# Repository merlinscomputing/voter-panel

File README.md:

# voter-panel
Voter display panel
Test Readme Changes
JJH-2052

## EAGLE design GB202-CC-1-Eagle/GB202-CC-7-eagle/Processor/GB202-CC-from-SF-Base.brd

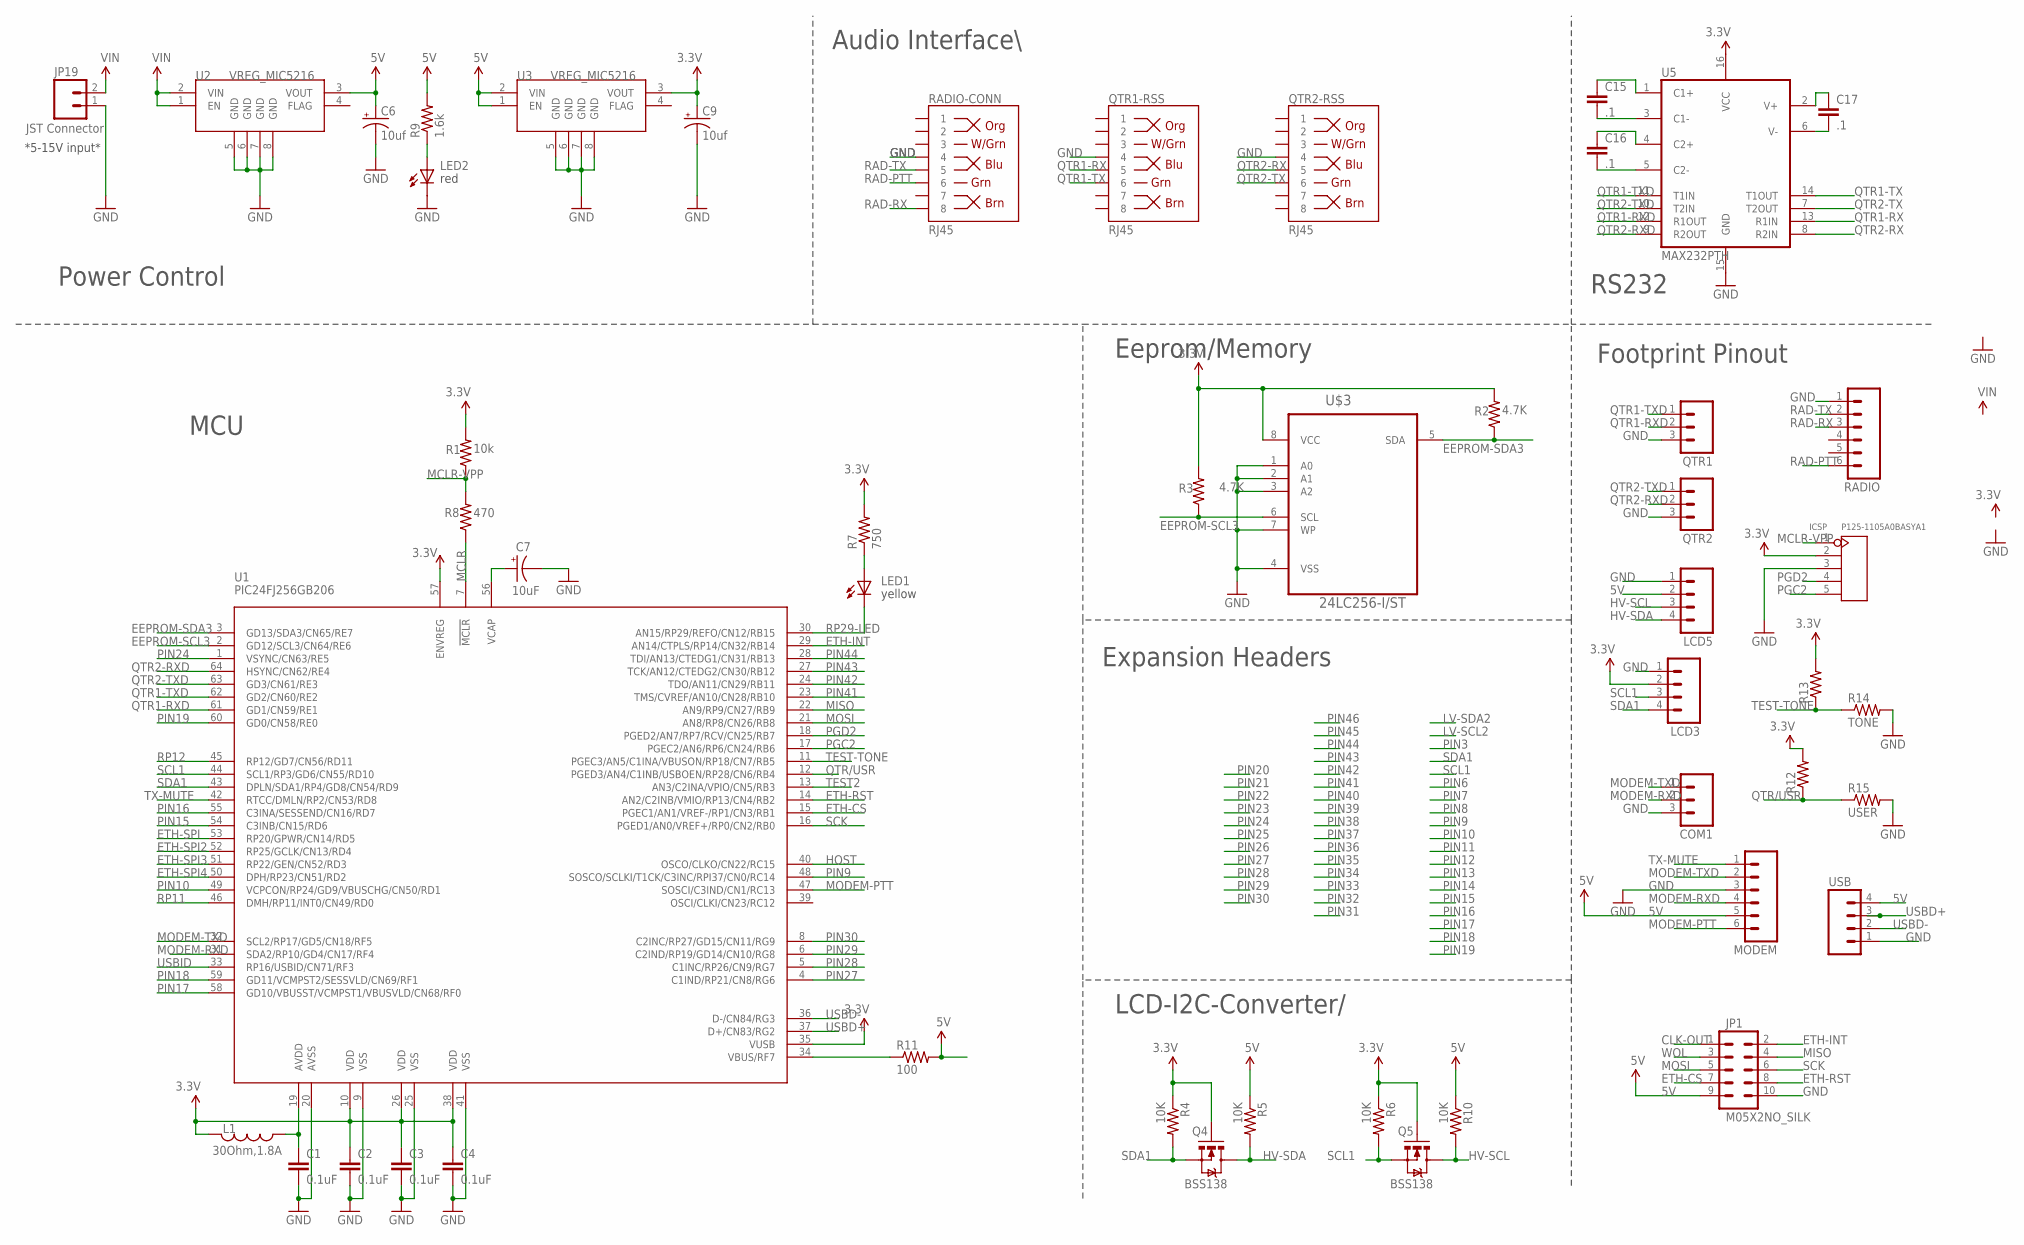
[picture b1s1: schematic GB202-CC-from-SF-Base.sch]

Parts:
C1, C2, C3, C4: 0.1uF; 0402-CAP
C6, C9: 10uf; EIA3216
C7: 10uF; EIA3216
C15, C16, C17: .1; CAP-PTH-SMALL
COM1: M031X03_NO_SILK; 1X03_NO_SILK
ICSP: P125-1105A0BASYA1; H5-2.54
JP1: M05X2NO_SILK; 2X5_NOSILK
JP19: JST Connector; JST-2-SMD
L1: 30Ohm,1.8A; 0603
LCD3, LCD5: M04LONGPADS; 1X04_LONGPADS
LED1: LY L29K-J1K2-26-Z; LED-0603
LED2: LS L29K-G1J2-1-Z; LED-0603
MODEM: M06LONGPADS; 1X06_LONGPADS
Q4, Q5: BSS138; SOT23-3
QTR1, QTR2: M031X03_NO_SILK; 1X03_NO_SILK
QTR1-RSS, QTR2-RSS: RJ45; RJ45-8
R1: 10k; R0402
R2, R3: 4.7K; R0402
R4, R6: 10K; 0402-RES
R5, R10: 10K; 0603-RES
R7: 750; 0603-RES
R8: 470; R0402
R9: 1.6k; 0603-RES
R11: 100; 0402-RES
R12, R13: R-US_R0402; R0402
R14: TONE; R1206
R15: USER; R1206
RADIO: M06LONGPADS; 1X06_LONGPADS
RADIO-CONN: RJ45; RJ45-8
U1: PIC24FJ256GB206; PIC24FXXX_TQFP64
U2, U3: VREG_MIC5216; MSOP8
U5: MAX232PTH; DIL16
U$3: 24LC256-I/ST; SOP65P638X110-8N
USB: M04PTH; 1X04

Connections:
3.3V: C2.1, C3.1, C4.1, C9.A (+), ICSP.2, L1.2, LCD3.2, Q4.1 (G), Q5.1 (G), R1.2, R2.2, R3.2, R4.1, R6.1, R7.2, R12.2, R13.2, U1.10 (VDD), U1.26 (VDD), U1.35 (VUSB), U1.38 (VDD), U1.57 (ENVREG), U3.3 (VOUT), U5.16 (VCC), U$3.8 (VCC)
5V: C6.A (+), JP1.9, LCD5.2, MODEM.5, R5.1, R9.2, R10.1, R11.2, U2.3 (VOUT), U3.1 (EN), U3.2 (VIN), USB.4
CLK-OUT: JP1.1
EEPROM-SCL3: R3.1, U1.2 (GD12/SCL3/CN64/RE6), U$3.6 (SCL)
EEPROM-SDA3: R2.1, U1.3 (GD13/SDA3/CN65/RE7), U$3.5 (SDA)
ETH-CS: JP1.7, U1.15 (PGEC1/AN1/VREF-/RP1/CN3/RB1)
ETH-INT: JP1.2, U1.29 (AN14/CTPLS/RP14/CN32/RB14)
ETH-RST: JP1.8, U1.14 (AN2/C2INB/VMIO/RP13/CN4/RB2)
ETH-SPI: U1.53 (RP20/GPWR/CN14/RD5)
ETH-SPI2: U1.52 (RP25/GCLK/CN13/RD4)
ETH-SPI3: U1.51 (RP22/GEN/CN52/RD3)
ETH-SPI4: U1.50 (DPH/RP23/CN51/RD2)
GND: C1.2, C2.2, C3.2, C4.2, C6.C (-), C7.C (-), C9.C (-), COM1.3, ICSP.3, JP1.10, JP19.1, LCD3.1, LCD5.1, LED2.C, MODEM.3, QTR1.3, QTR1-RSS.4, QTR2.3, QTR2-RSS.4, R14.2, R15.2, RADIO.1, RADIO-CONN.4, U1.9 (VSS), U1.20 (AVSS), U1.25 (VSS), U1.41 (VSS), U2.5 (GND), U2.6 (GND), U2.7 (GND), U2.8 (GND), U3.5 (GND), U3.6 (GND), U3.7 (GND), U3.8 (GND), U5.15 (GND), U$3.1 (A0), U$3.2 (A1), U$3.3 (A2), U$3.4 (VSS), U$3.7 (WP), USB.1
HOST: U1.40 (OSCO/CLKO/CN22/RC15)
HV-SCL: LCD5.3, Q5.3 (D), R10.2
HV-SDA: LCD5.4, Q4.3 (D), R5.2
MCLR: R8.1, U1.7 (!MCLR)
MCLR-VPP: ICSP.1, R1.1, R8.2
MISO: JP1.4, U1.22 (AN9/RP9/CN27/RB9)
MODEM-PTT: MODEM.6, U1.47 (SOSCI/C3IND/CN1/RC13)
MODEM-RXD: COM1.2, MODEM.4, U1.31 (SDA2/RP10/GD4/CN17/RF4)
MODEM-TXD: COM1.1, MODEM.2, U1.32 (SCL2/RP17/GD5/CN18/RF5)
MOSI: JP1.5, U1.21 (AN8/RP8/CN26/RB8)
unnamed: LED1.A, R7.1
unnamed: LED2.A, R9.1
unnamed: C7.A (+), U1.56 (VCAP)
unnamed: C1.1, L1.1, U1.19 (AVDD)
unnamed: R11.1, U1.34 (VBUS/RF7)
unnamed: C15.1, U5.1 (C1+)
unnamed: C15.2, U5.3 (C1-)
unnamed: C16.1, U5.4 (C2+)
unnamed: C16.2, U5.5 (C2-)
unnamed: C17.2, U5.6 (V-)
unnamed: C17.1, U5.2 (V+)
PGC2: ICSP.5, U1.17 (PGEC2/AN6/RP6/CN24/RB6)
PGD2: ICSP.4, U1.18 (PGED2/AN7/RP7/RCV/CN25/RB7)
PIN9: U1.48 (SOSCO/SCLKI/T1CK/C3INC/RPI37/CN0/RC14)
PIN10: U1.49 (VCPCON/RP24/GD9/VBUSCHG/CN50/RD1)
PIN15: U1.54 (C3INB/CN15/RD6)
PIN16: U1.55 (C3INA/SESSEND/CN16/RD7)
PIN17: U1.58 (GD10/VBUSST/VCMPST1/VBUSVLD/CN68/RF0)
PIN18: U1.59 (GD11/VCMPST2/SESSVLD/CN69/RF1)
PIN19: U1.60 (GD0/CN58/RE0)
PIN24: U1.1 (VSYNC/CN63/RE5)
PIN27: U1.4 (C1IND/RP21/CN8/RG6)
PIN28: U1.5 (C1INC/RP26/CN9/RG7)
PIN29: U1.6 (C2IND/RP19/GD14/CN10/RG8)
PIN30: U1.8 (C2INC/RP27/GD15/CN11/RG9)
PIN41: U1.23 (TMS/CVREF/AN10/CN28/RB10)
PIN42: U1.24 (TDO/AN11/CN29/RB11)
PIN43: U1.27 (TCK/AN12/CTEDG2/CN30/RB12)
PIN44: U1.28 (TDI/AN13/CTEDG1/CN31/RB13)
QTR1-RX: QTR1-RSS.5, U5.13 (R1IN)
QTR1-RXD: QTR1.2, U1.61 (GD1/CN59/RE1), U5.12 (R1OUT)
QTR1-TX: QTR1-RSS.6, U5.14 (T1OUT)
QTR1-TXD: QTR1.1, U1.62 (GD2/CN60/RE2), U5.11 (T1IN)
QTR2-RX: QTR2-RSS.5, U5.8 (R2IN)
QTR2-RXD: QTR2.2, U1.64 (HSYNC/CN62/RE4), U5.9 (R2OUT)
QTR2-TX: QTR2-RSS.6, U5.7 (T2OUT)
QTR2-TXD: QTR2.1, U1.63 (GD3/CN61/RE3), U5.10 (T2IN)
QTR/USR: R12.1, R15.1, U1.12 (PGED3/AN4/C1INB/USBOEN/RP28/CN6/RB4)
RAD-PTT: RADIO.6, RADIO-CONN.6
RAD-RX: RADIO.3, RADIO-CONN.8
RAD-TX: RADIO.2, RADIO-CONN.5
RP11: U1.46 (DMH/RP11/INT0/CN49/RD0)
RP12: U1.45 (RP12/GD7/CN56/RD11)
RP29-LED: LED1.C, U1.30 (AN15/RP29/REFO/CN12/RB15)
SCK: JP1.6, U1.16 (PGED1/AN0/VREF+/RP0/CN2/RB0)
SCL1: LCD3.3, Q5.2 (S), R6.2, U1.44 (SCL1/RP3/GD6/CN55/RD10)
SDA1: LCD3.4, Q4.2 (S), R4.2, U1.43 (DPLN/SDA1/RP4/GD8/CN54/RD9)
TEST2: U1.13 (AN3/C2INA/VPIO/CN5/RB3)
TEST-TONE: R13.1, R14.1, U1.11 (PGEC3/AN5/C1INA/VBUSON/RP18/CN7/RB5)
TX-MUTE: MODEM.1, U1.42 (RTCC/DMLN/RP2/CN53/RD8)
USBD+: U1.37 (D+/CN83/RG2), USB.3
USBD-: U1.36 (D-/CN84/RG3), USB.2
USBID: U1.33 (RP16/USBID/CN71/RF3)
VIN: JP19.2, U2.1 (EN), U2.2 (VIN)
WOL: JP1.3

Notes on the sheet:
*5-15V input*
yellow
red
Footprint Pinout
Power Control
MCU
RS232
Audio Interface\
LCD-I2C-Converter/
Expansion Headers
Eeprom/Memory

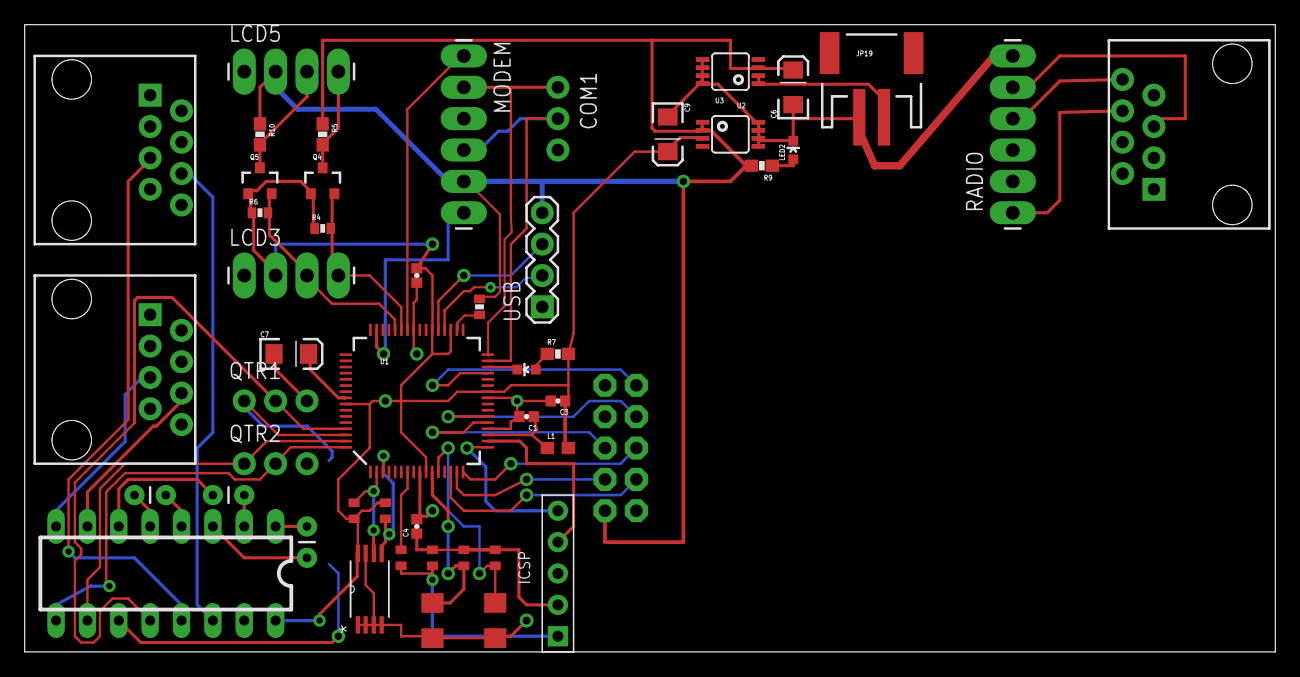
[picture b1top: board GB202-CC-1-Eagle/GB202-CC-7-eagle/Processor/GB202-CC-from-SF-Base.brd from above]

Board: 2 copper layers, 101.3 x 50.8 mm, 49 parts (0 on the bottom side), 51 nets.

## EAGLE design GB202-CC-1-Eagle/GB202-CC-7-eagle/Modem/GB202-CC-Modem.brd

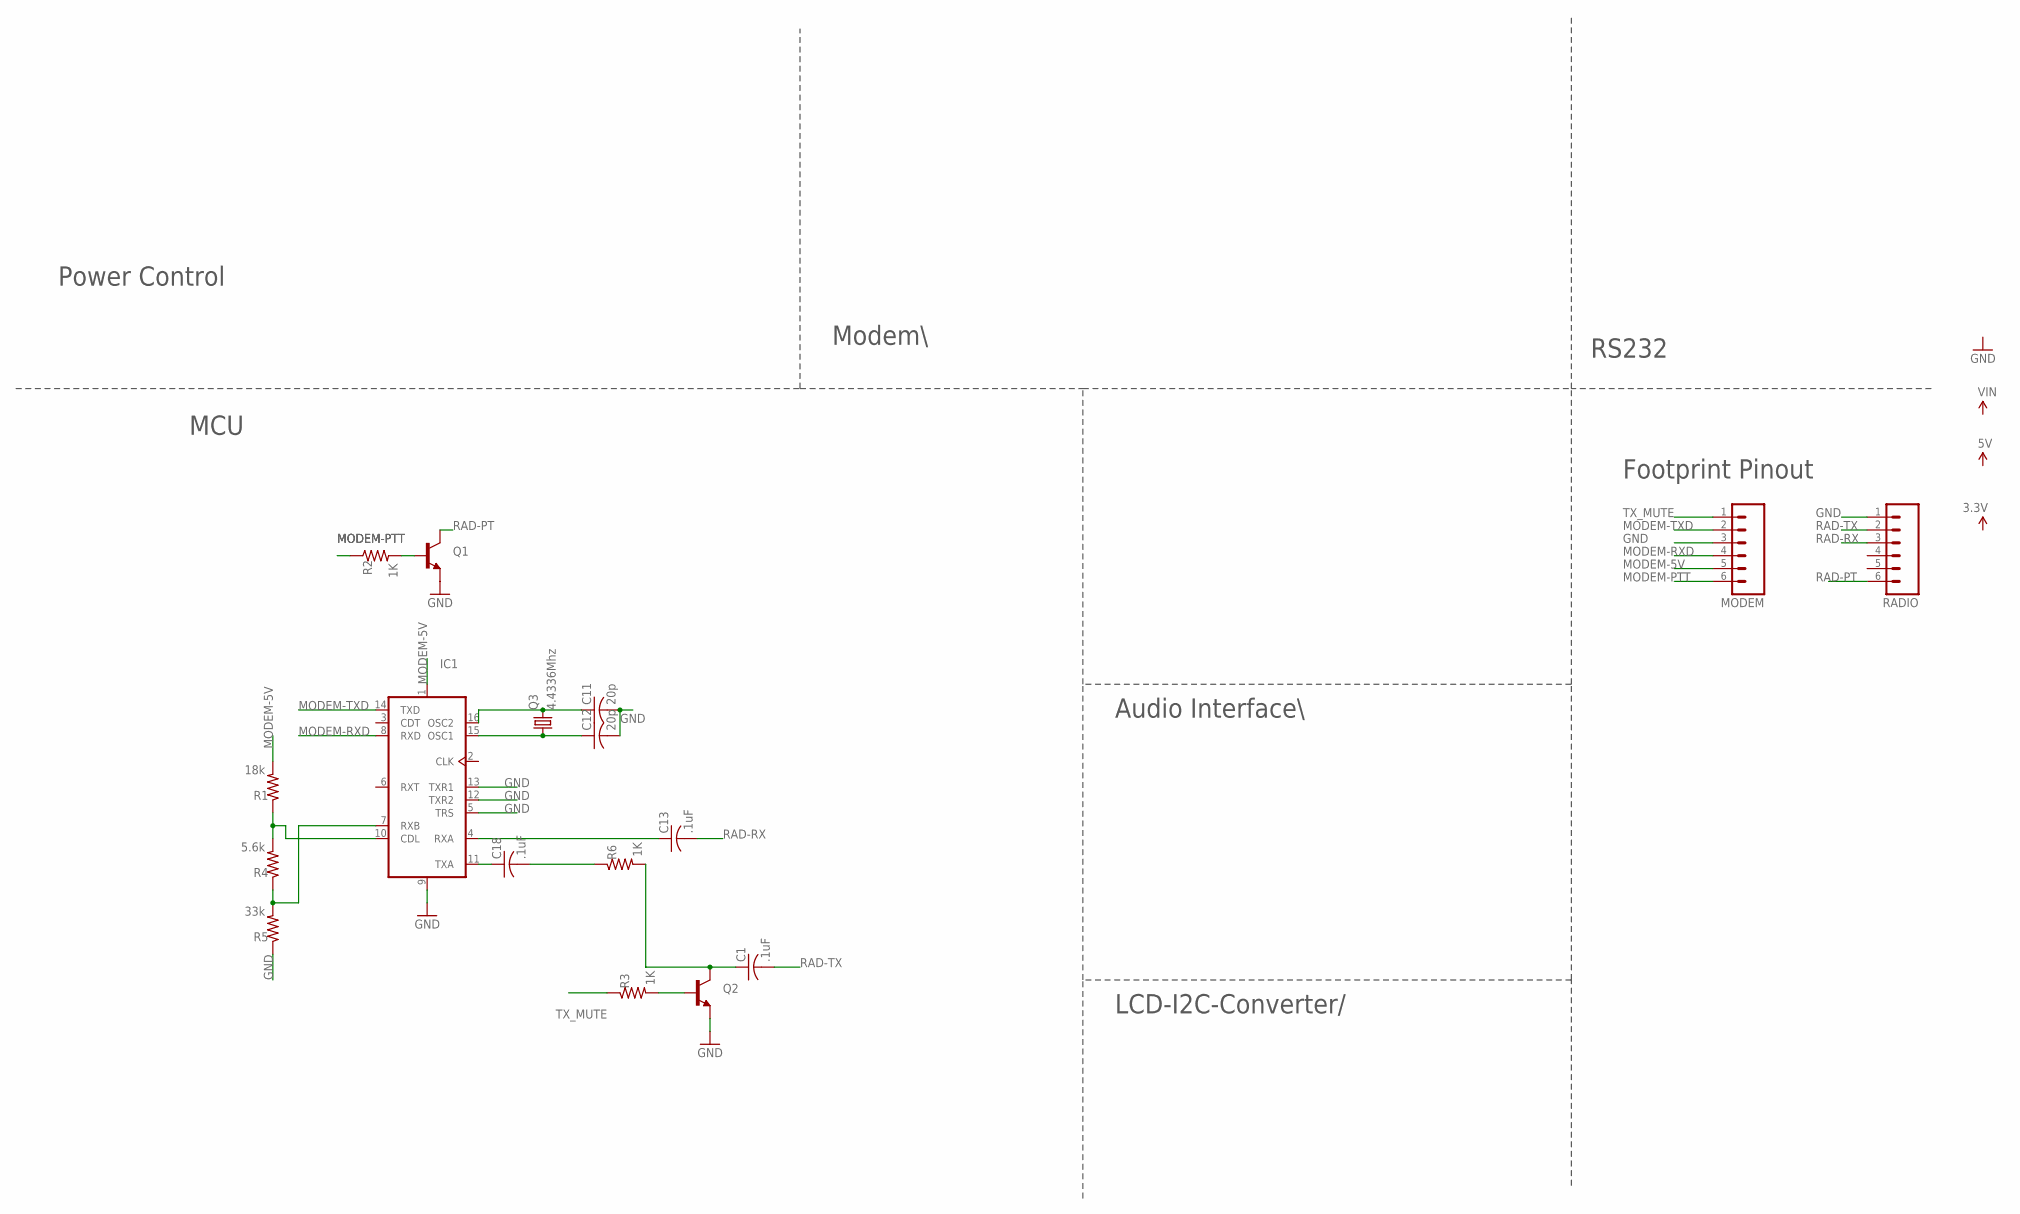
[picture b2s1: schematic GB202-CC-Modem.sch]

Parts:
C1, C13, C18: .1uF; C050-024X044
C11, C12: 20p; C0603
IC1: TCM3105; DIL16
MODEM: M06LONGPADS; 1X06_LONGPADS
Q1: TRANSISTOR_NPNP2N2222A; TO-92
Q2: TRANSISTOR_NPN2N3904; TO-92
Q3: 4.4336Mhz; HC49/S
R1: 18k; AXIAL-0.3
R2, R3, R6: 1K; AXIAL-0.3
R4: 5.6k; AXIAL-0.3
R5: 33k; AXIAL-0.3-KIT
RADIO: M06LONGPADS; 1X06_LONGPADS

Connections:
GND: C11.2, C12.2, IC1.5 (TRS), IC1.9 (VSS), IC1.12 (TXR2), IC1.13 (TXR1), MODEM.3, Q1.3 (E), Q2.1 (E), R5.P$1 (1), RADIO.1
MODEM-5V: IC1.1 (VDD), MODEM.5, R1.P$2 (2)
MODEM-PTT: MODEM.6, R2.P$1 (1)
MODEM-RXD: IC1.8 (RXD), MODEM.4
MODEM-TXD: IC1.14 (TXD), MODEM.2
unnamed: Q1.2 (B), R2.P$2 (2)
unnamed: C1.1, Q2.3 (C), R6.P$2 (2)
unnamed: Q2.2 (B), R3.P$2 (2)
unnamed: C11.1, IC1.16 (OSC2), Q3.2
unnamed: C12.1, IC1.15 (OSC1), Q3.1
unnamed: C13.1, IC1.4 (RXA)
unnamed: IC1.10 (CDL), R1.P$1 (1), R4.P$2 (2)
unnamed: IC1.7 (RXB), R4.P$1 (1), R5.P$2 (2)
unnamed: C18.1, IC1.11 (TXA)
unnamed: C18.2, R6.P$1 (1)
RAD-PT: Q1.1 (C), RADIO.6
RAD-RX: C13.2, RADIO.3
RAD-TX: C1.2, RADIO.2
TX_MUTE: MODEM.1, R3.P$1 (1)

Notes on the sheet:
Footprint Pinout
Power Control
MCU
RS232
Modem\
Audio Interface\
LCD-I2C-Converter/

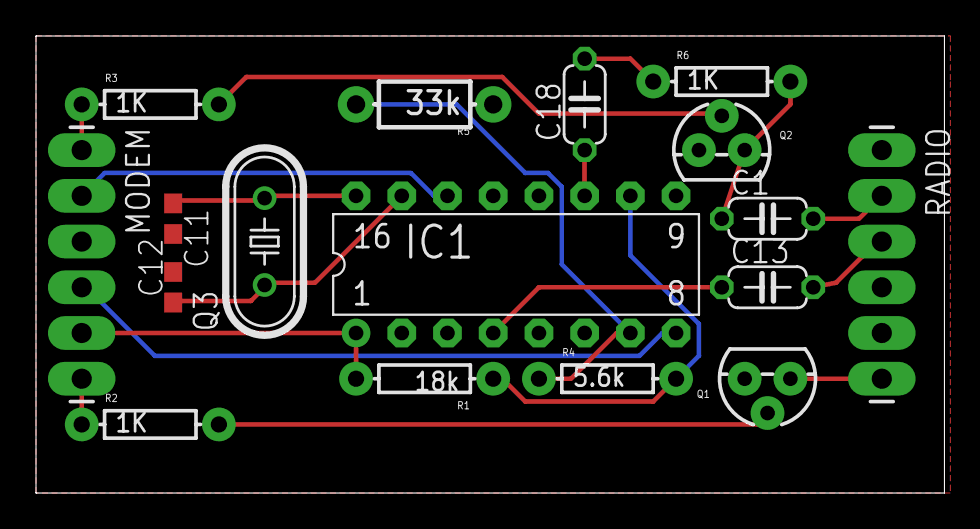
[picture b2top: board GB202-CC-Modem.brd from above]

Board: 2 copper layers, 50.5 x 25.4 mm, 17 parts (0 on the bottom side), 19 nets.

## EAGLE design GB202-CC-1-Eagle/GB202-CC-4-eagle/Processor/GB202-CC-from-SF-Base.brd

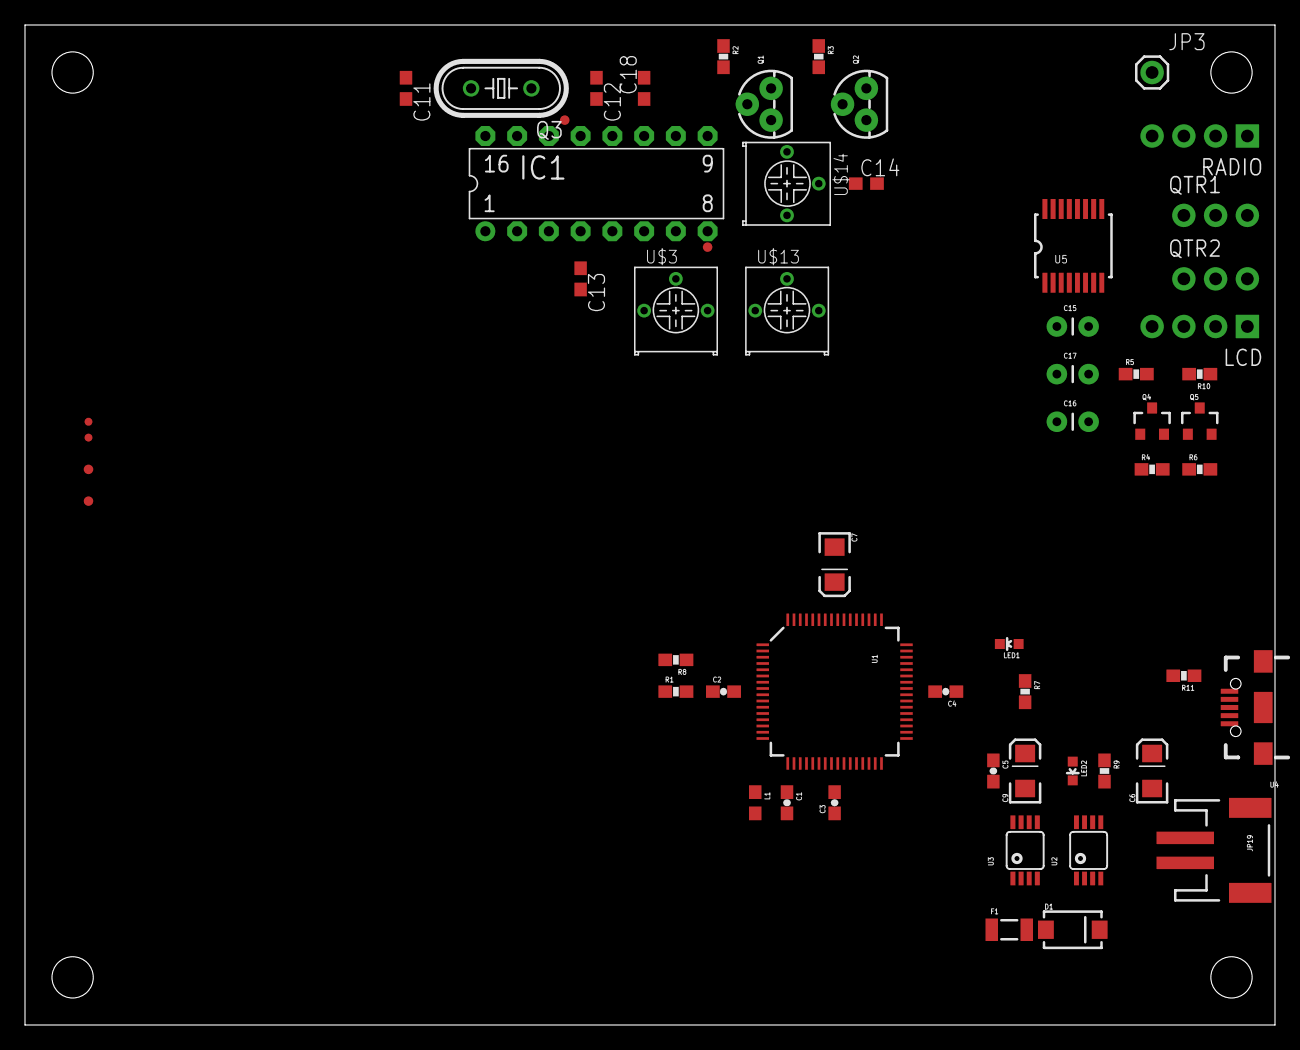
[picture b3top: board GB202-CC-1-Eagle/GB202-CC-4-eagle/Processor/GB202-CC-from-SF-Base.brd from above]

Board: 2 copper layers, 100.0 x 80.0 mm, 62 parts (0 on the bottom side), 45 nets, no tracks yet.

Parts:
C1, C2, C3, C4, C5: 0.1uF; 0603-CAP
C6, C9: 10uf; EIA3216
C7: 10uF; EIA3216
C11, C12: C0603
C13, C14, C18: .1uF; C0603
C15, C16, C17: .1; CAP-PTH-SMALL
D1: DIODE-SCHOTTKY_; SMA-DIODE
F1: PTCSMD; PTC-1206
IC1: DIL16
JP3: M01PTH; 1X01
JP8, JP16: FIDUCIALUFIDUCIAL; MICRO-FIDUCIAL
JP10, JP11, JP12, JP13: STAND-OFF
JP19: JST Connector; JST-2-SMD
L1: 30Ohm,1.8A; 0603
LCD: 1X04_NO_SILK
LED1: LY L29K-J1K2-26-Z; LED-0603
LED2: LS L29K-G1J2-1-Z; LED-0603
Q1, Q2: TO-92
Q3: 4.4336Mhz; HC49/S
Q4, Q5: BSS138; SOT23-3
QTR1, QTR2: 1X03_NO_SILK
R1: 10k; 0603-RES
R2, R3: 1K; 0603-RES
R4, R5, R6, R10: 10K; 0603-RES
R7: 750; 0603-RES
R8: 470; 0603-RES
R9: 1.6k; 0603-RES
R11: DNP; 0603-RES
RADIO: 1X04_NO_SILK
TP5, TP6, TP7, TP8: TEST-POINT3; PAD.03X.03
U1: PIC24FJ256GB206; PIC24FXXX_TQFP64
U2, U3: VREG_MIC5216; MSOP8
U4: USB-AB-MICRO-SMD_V03
U5: MAX232TSSOP; TSSOP16
U$3, U$13, U$14: RTRIM-3362P; RTRIM3362P

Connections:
3.3V: C2.1, C3.1, C4.1, C5.1, C9.A, L1.2, Q4.1, Q5.1, R1.2, R4.1, R6.1, R7.2, U1.10, U1.26, U1.35, U1.38, U1.57, U3.3, U5.16
5V: C6.A, D1.C, IC1.1, LCD.2, R5.1, R9.2, R10.1, U2.3, U3.1, U3.2
+5.0: U$3.3, U$13.3
BOOT: LED1.C, U1.39
D+: U1.37, U4.D+1
D-: U1.36, U4.D-1
GND: C1.2, C2.2, C3.2, C4.2, C5.2, C6.C, C7.C, C9.C, C11.2, C12.2, IC1.5, IC1.9, IC1.12, IC1.13, JP3.1, JP19.1, LCD.1, LED2.C, Q1.1, Q2.1, QTR1.3, QTR2.3, R11.1, RADIO.2, U1.9, U1.20, U1.25, U1.41, U2.5, U2.6, U2.7, U2.8, U3.5, U3.6, U3.7, U3.8, U4.GND1, U5.15, U$3.1, U$13.1, U$14.1
HV-SCL: LCD.3, Q5.3, R10.2
HV-SDA: LCD.4, Q4.3, R5.2
LV-SCL: Q5.2, R6.2
LV-SDA: Q4.2, R4.2
MCLR: R8.1, U1.7
unnamed: Q1.2, R2.2
unnamed: LED1.A, R7.1
unnamed: LED2.A, R9.1
unnamed: D1.A, F1.2
unnamed: C7.A, U1.56
unnamed: Q2.2, R3.2
unnamed: C1.1, L1.1, U1.19
unnamed: C11.1, IC1.16, Q3.2
unnamed: C12.1, IC1.15, Q3.1
unnamed: C13.1, IC1.4
unnamed: C14.1, U$14.2
unnamed: IC1.10, U$13.2
unnamed: IC1.7, U$3.2
unnamed: C18.1, IC1.11
unnamed: C18.2, U$14.3
unnamed: C15.1, U5.1
unnamed: C15.2, U5.3
unnamed: C16.1, U5.4
unnamed: C16.2, U5.5
unnamed: C17.2, U5.6
unnamed: C17.1, U5.2
P7: R1.1, R8.2
QTR1-RX: QTR1.2, U5.13
QTR1-TX: QTR1.1, U5.14
QTR2-RX: QTR2.2, U5.8
QTR2-TX: QTR2.1, U5.7
RAD-RX: C13.2, RADIO.1
RAD-TX: Q2.3, RADIO.3
TCM-RXD: IC1.8, TP6.P$1
TCM-TXD: IC1.14, TP5.P$1
USBID: R11.2, U1.33, U4.ID1
VBUS: F1.1, U1.34, U4.VBUS1
VIN: JP19.2, U2.1, U2.2

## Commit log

2017-02-12 Commit initial readme changes
2017-02-12 Import from SVN - use 7
    Initial commit from GB202 Coverage tester SVN repo
2017-02-12 cleanup1
    Remove Eagle folders

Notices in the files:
parts and their libraries:
SparkFun-PowerIC: Licensing: CC v3.0 Share-Alike You are welcome to use this library for commercial purposes.
GeekAmmo: Licensing:Creative Commons ShareAlike 4.0 International - https://creativecommons.org/licenses/by-sa/4.0
